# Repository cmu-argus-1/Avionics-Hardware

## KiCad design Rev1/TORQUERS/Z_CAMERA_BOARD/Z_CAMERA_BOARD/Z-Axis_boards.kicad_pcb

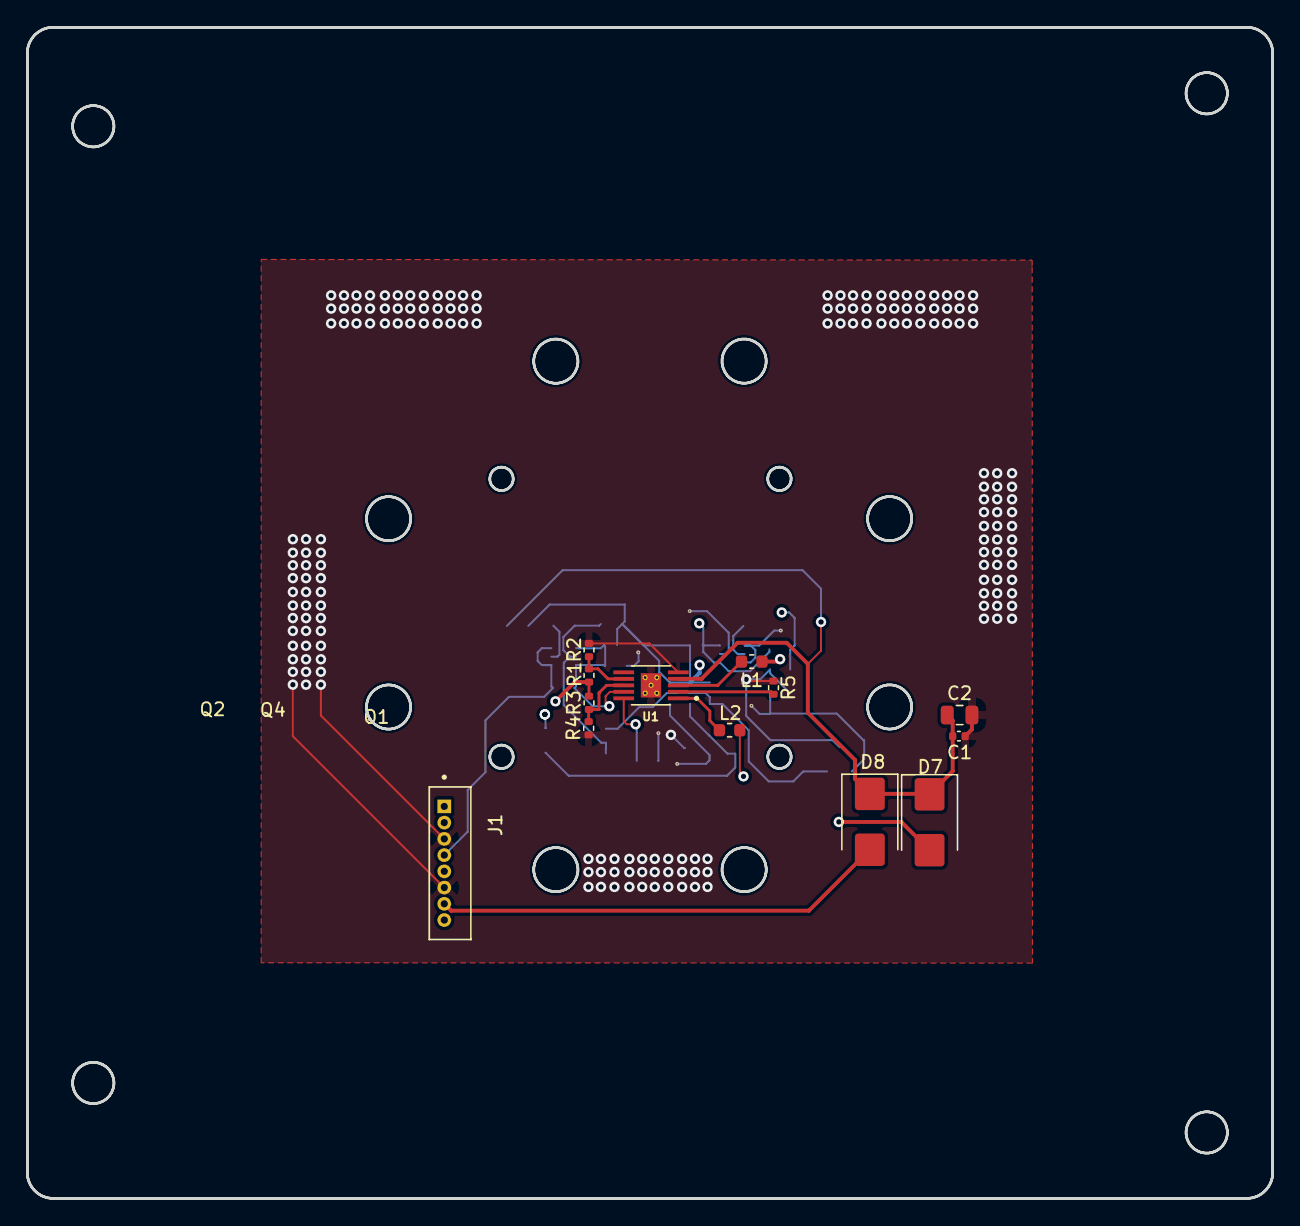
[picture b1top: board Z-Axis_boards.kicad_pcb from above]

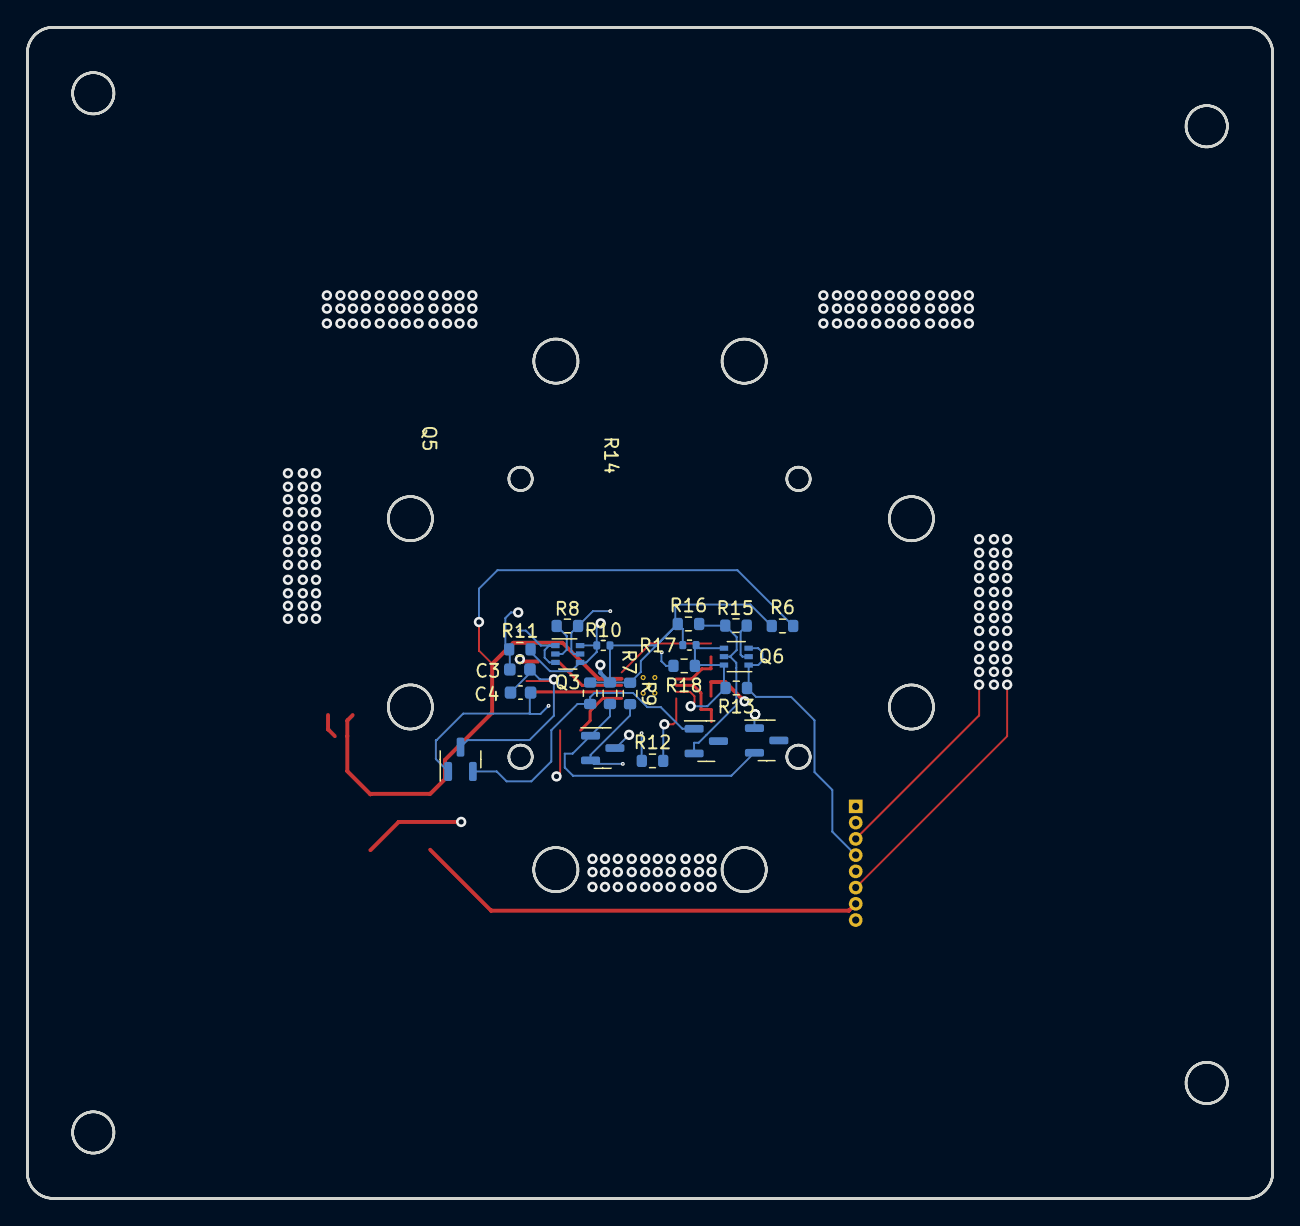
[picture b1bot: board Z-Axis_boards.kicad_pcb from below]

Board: 8 copper layers, 95.9 x 90.2 mm, 34 parts (21 on the bottom side), 22 nets.

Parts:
C1: 0.1uF; C_0402_1005Metric
C2: 10uF; C_0805_2012Metric
C3, C4: 10nF; C_0603_1608Metric
D7, D8: B220; D_SMB
J1: 0530470810; MOLEX_0530470810
L1, L2: TBD; L_0603_1608Metric
Q1, Q2, Q4, Q5: BSS138; SOT-23
Q3, Q6: MBT2222ADW1T1; SOT-363_SC-70-6
R1, R2, R3, R4, R5: 0; R_0402_1005Metric
R6, R12, R13: 0; R_0603_1608Metric
R7, R9, R14, R16: 10K; R_0603_1608Metric
R8, R15: 600; R_0603_1608Metric
R10, R17: 10K; R_0402_1005Metric
R11, R18: 100K; R_0603_1608Metric
U1: DRV8830DGQ; IC_XTR111AIDGQR

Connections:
+3.3V: D7.2 (A), J1.8, R1.2, R3.2, R6.1, R7.2, R9.1, R10.2, R14.2, R16.1, R17.2
/coils: L1.1, L2.1
GND: C1.2, C2.2, C3.2, C4.2, J1.3, J1.6, Q1.3 (D), Q2.3 (D), Q4.3 (D), Q5.3 (D), R2.1, R4.1, R5.2, U1.5 (GND), U1.11 (EP)
unnamed: C1.1, C2.1, D7.1 (K), D8.1 (K), R6.2, U1.4 (VCC)
unnamed: Q1.1 (G), Q2.2 (S), R7.1
unnamed: Q1.2 (S), Q3.5 (B2), R8.1, R9.2
unnamed: C3.1, Q2.1 (G), R11.1
unnamed: Q3.2 (B1), R8.2
unnamed: Q4.1 (G), Q5.2 (S), R14.1
unnamed: Q4.2 (S), Q6.5 (B2), R15.2, R16.2
unnamed: C4.1, Q5.1 (G), R18.1
unnamed: Q6.2 (B1), R15.1
unnamed: R1.1, R2.2, U1.7 (A0)
unnamed: R3.1, R4.2, U1.8 (A1)
unnamed: R5.1, U1.2 (ISENSE)
unnamed: L1.2, U1.3 (OUT1)
unnamed: L2.2, U1.1 (OUT2)
SCL: Q3.4 (E2), Q3.6 (C1), R10.1, R11.2, R12.2, U1.10 (SCL)
SCL1_b4iso: J1.5, Q3.1 (E1), Q3.3 (C2), R12.1
SDA: Q6.4 (E2), Q6.6 (C1), R13.2, R17.1, R18.2, U1.9 (SDA)
SDA1_b4iso: J1.4, Q6.1 (E1), Q6.3 (C2), R13.1
VBATT: D8.2 (A), J1.7

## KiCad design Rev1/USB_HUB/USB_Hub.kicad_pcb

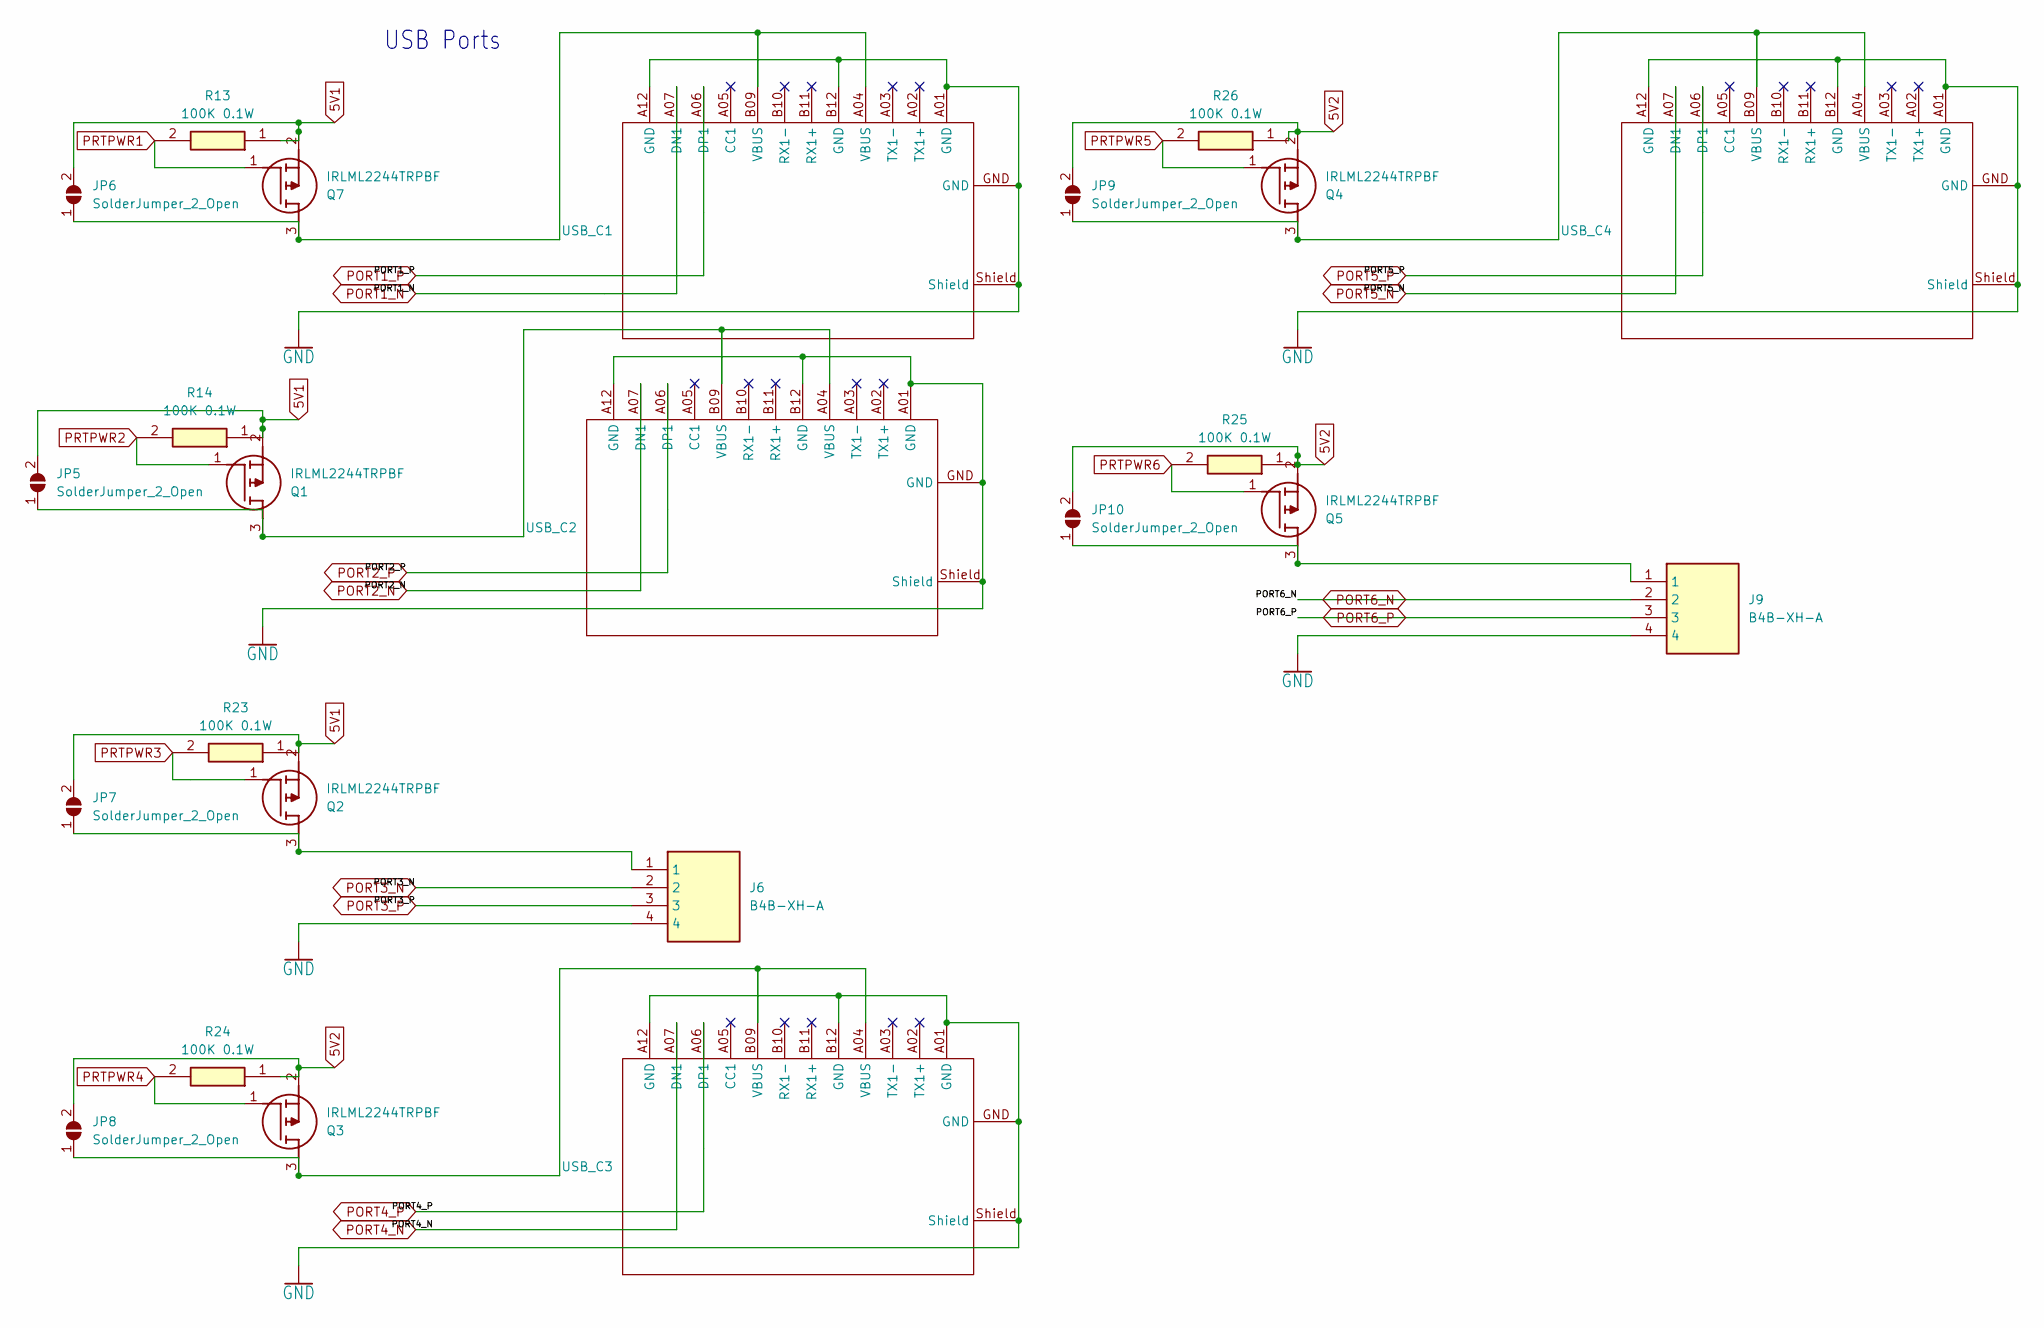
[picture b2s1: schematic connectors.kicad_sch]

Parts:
J6, J9: B4B-XH-A; B4BXHA; Manufacturer_Part_Number B4B-XH-A
JP5, JP6, JP7, JP8, JP9, JP10: SolderJumper_2_Open; SolderJumper-2_P1.3mm_Open_Pad1.0x1.5mm
Q1, Q2, Q3, Q4, Q5, Q7: IRLML2244TRPBF; SOT95P237X112-3N; Manufacturer_Part_Number IRLML2244TRPBF; Mouser Part Number 942-IRLML2244TRPBF
R13, R14, R23, R24, R25, R26: 100K 0.1W; RESC1608X55N; Manufacturer_Part_Number RMCF0603FT100K; Mouser Part Number 708-RMCF0603FT100K
USB_C1, USB_C2, USB_C3, USB_C4: PLUG-USBC-121SMT-4BS2S

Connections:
5V1: JP5.2 (B), JP6.2 (B), JP7.2 (B), Q1.2 (S), Q2.2 (S), Q7.2 (S), R13.1, R14.1, R23.1; also elsewhere on the board
5V2: JP8.2 (B), JP9.2 (B), JP10.2 (B), Q3.2 (S), Q4.2 (S), Q5.2 (S), R24.1, R25.1, R26.1; also elsewhere on the board
GND: J6.4, J9.4, USB_C1.A01 (GND), USB_C1.A12 (GND), USB_C1.B12 (GND), USB_C1.GND, USB_C1.Shield, USB_C2.A01 (GND), USB_C2.A12 (GND), USB_C2.B12 (GND), USB_C2.GND, USB_C2.Shield, USB_C3.A01 (GND), USB_C3.A12 (GND), USB_C3.B12 (GND), USB_C3.GND, USB_C3.Shield, USB_C4.A01 (GND), USB_C4.A12 (GND), USB_C4.B12 (GND), USB_C4.GND, USB_C4.Shield; also elsewhere on the board
unnamed: JP5.1 (A), Q1.3 (D), USB_C2.A04 (VBUS), USB_C2.B09 (VBUS)
unnamed: JP6.1 (A), Q7.3 (D), USB_C1.A04 (VBUS), USB_C1.B09 (VBUS)
unnamed: J6.1, JP7.1 (A), Q2.3 (D)
unnamed: JP8.1 (A), Q3.3 (D), USB_C3.A04 (VBUS), USB_C3.B09 (VBUS)
unnamed: JP9.1 (A), Q4.3 (D), USB_C4.A04 (VBUS), USB_C4.B09 (VBUS)
unnamed: J9.1, JP10.1 (A), Q5.3 (D)
PORT1_N: USB_C1.A07 (DN1); also elsewhere on the board
PORT1_P: USB_C1.A06 (DP1); also elsewhere on the board
PORT2_N: USB_C2.A07 (DN1); also elsewhere on the board
PORT2_P: USB_C2.A06 (DP1); also elsewhere on the board
PORT3_N: J6.2; also elsewhere on the board
PORT3_P: J6.3; also elsewhere on the board
PORT4_N: USB_C3.A07 (DN1); also elsewhere on the board
PORT4_P: USB_C3.A06 (DP1); also elsewhere on the board
PORT5_N: USB_C4.A07 (DN1); also elsewhere on the board
PORT5_P: USB_C4.A06 (DP1); also elsewhere on the board
PORT6_N: J9.2; also elsewhere on the board
PORT6_P: J9.3; also elsewhere on the board
PRTPWR1: Q7.1 (G), R13.2; also elsewhere on the board
PRTPWR2: Q1.1 (G), R14.2; also elsewhere on the board
PRTPWR3: Q2.1 (G), R23.2; also elsewhere on the board
PRTPWR4: Q3.1 (G), R24.2; also elsewhere on the board
PRTPWR5: Q4.1 (G), R26.2; also elsewhere on the board
PRTPWR6: Q5.1 (G), R25.2; also elsewhere on the board

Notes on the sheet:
USB Ports

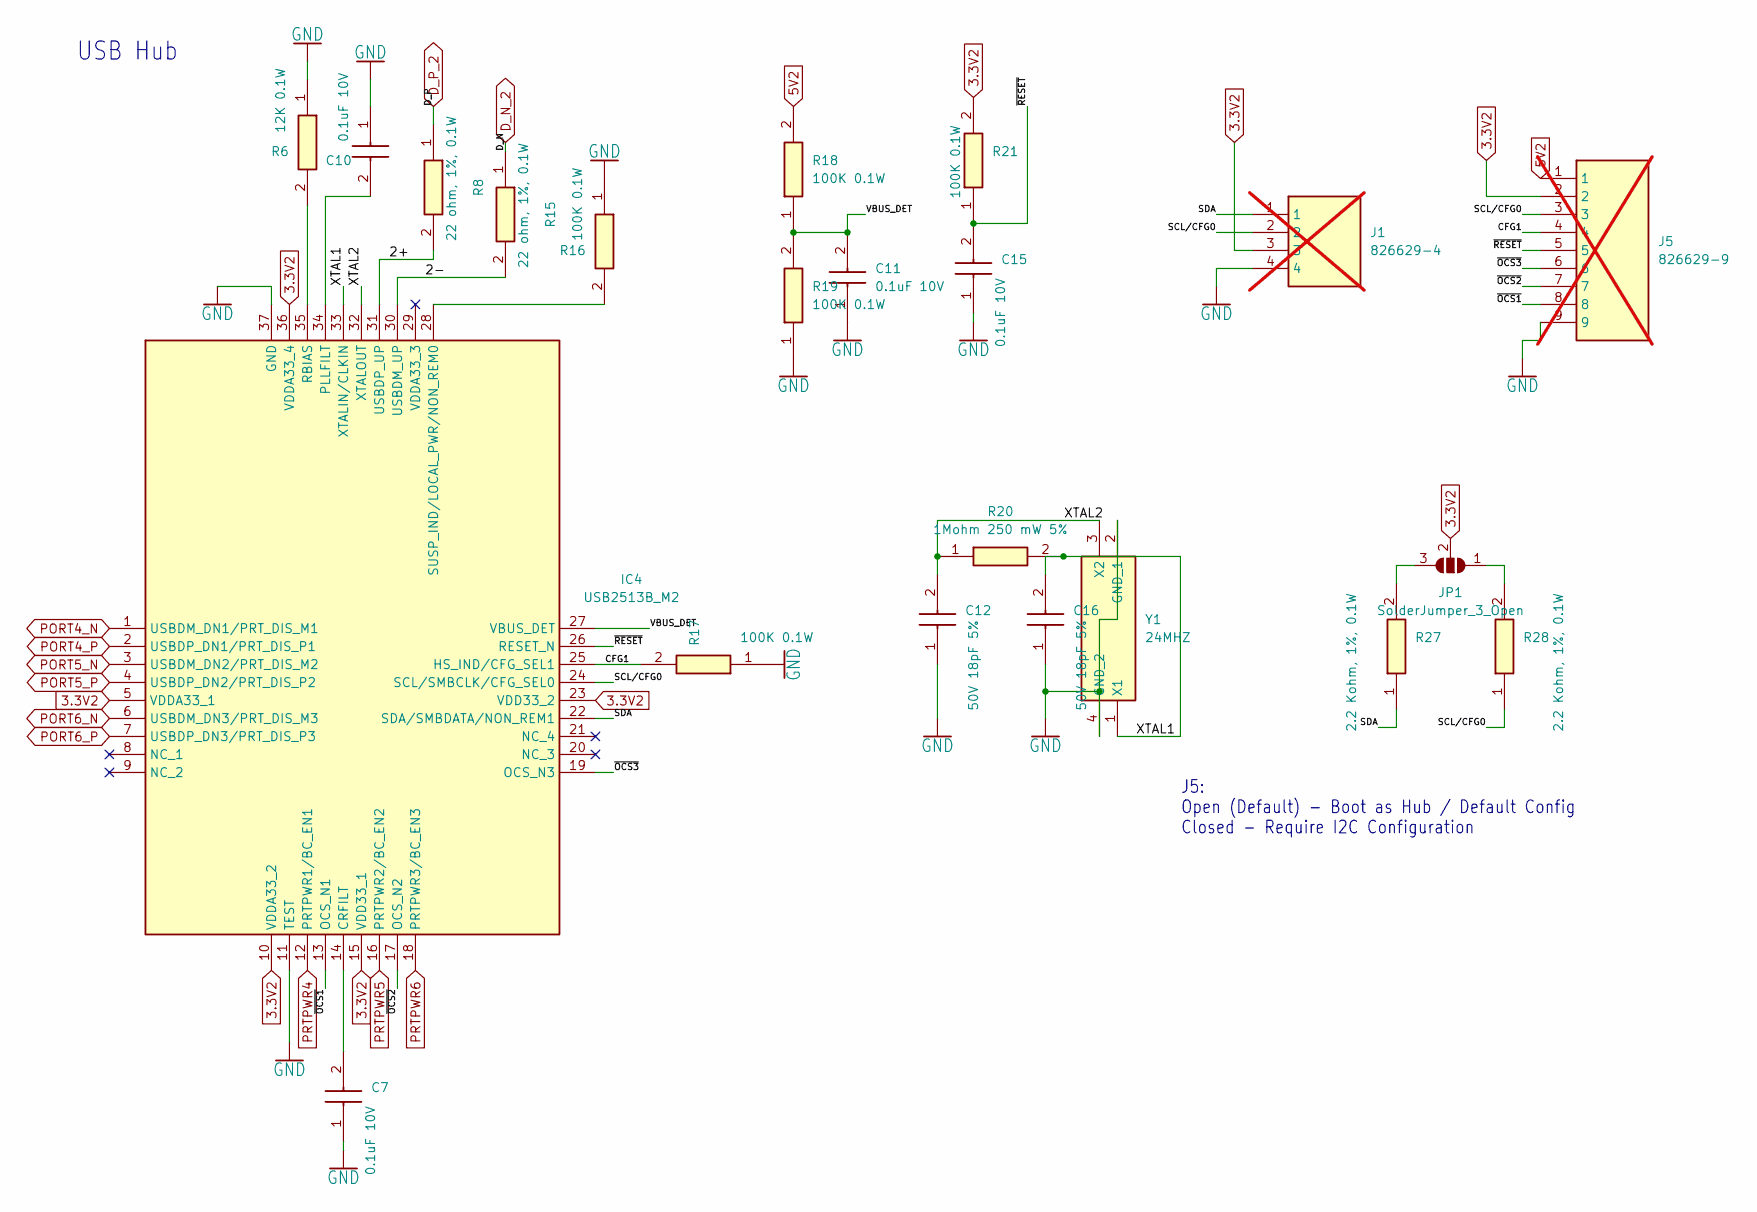
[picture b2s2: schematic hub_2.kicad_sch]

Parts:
C7, C10, C11, C15: 0.1uF 10V; CAPC1608X87N; Manufacturer_Part_Number C0603T104K8RAC7867; Mouser Part Number 80-C0603T104K8RACTU
C12, C16: 50V 18pF 5%; CAPC1608X90N; Manufacturer_Part_Number 06035A180J4T2A; Mouser Part Number 581-06035A180J4T2A
IC4: USB2513B_M2; QFN50P600X600X100-37N-D; Manufacturer_Part_Number USB2513B/M2; Mouser Part Number 579-USB2513B/M2
J1: 826629-4; HDRV4W63P0X254_1X4_1016X250X950P; Manufacturer_Part_Number 826629-4; Mouser Part Number 571-826629-4; not fitted
J5: 826629-9; HDRV9W63P0X254_1X9_2286X250X950P; Manufacturer_Part_Number 826629-9; Mouser Part Number 571-826629-9; not fitted
JP1: SolderJumper_3_Open; SolderJumper-3_P1.3mm_Open_Pad1.0x1.5mm_NumberLabels
R6: 12K 0.1W; RESC1608X55N; Manufacturer_Part_Number RMCF0603FT12K0
R8, R15: 22 ohm, 1%, 0.1W; RESC1608X55N; Manufacturer_Part_Number RMCF0603FT22R0
R16, R17, R18, R19, R21: 100K 0.1W; RESC1608X55N; Manufacturer_Part_Number RMCF0603FT100K; Mouser Part Number 708-RMCF0603FT100K
R20: 1Mohm 250 mW 5%; ERJP03_PA3__0603_; Manufacturer_Part_Number ERJ-PA3J105V; Mouser Part Number 667-ERJ-PA3J105V
R27, R28: 2.2 Kohm, 1%, 0.1W; RESC1608X55N; Manufacturer_Part_Number RMCF0603FT2K20
Y1: 24MHZ; ABM10W240000MHZ8K1ZT3; Manufacturer_Part_Number ABM10W-24.0000MHZ-7-B1U-T3

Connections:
3.3V2: IC4.5 (VDDA33_1), IC4.10 (VDDA33_2), IC4.15 (VDD33_1), IC4.23 (VDD33_2), IC4.36 (VDDA33_4), J1.3, J5.2, JP1.2 (C), R21.2; also elsewhere on the board
5V2: J5.1, R18.2; also elsewhere on the board
/hub_2/2+: IC4.31 (USBDP_UP), R8.2
/hub_2/2-: IC4.30 (USBDM_UP), R15.2
/hub_2/CFG1: IC4.25 (HS_IND/CFG_SEL1), J5.4, R17.2
/hub_2/SCL/CFG0: IC4.24 (SCL/SMBCLK/CFG_SEL0), J1.2, J5.3, R28.1
/hub_2/SDA: IC4.22 (SDA/SMBDATA/NON_REM1), J1.1, R27.1
/hub_2/VBUS_DET: C11.2, IC4.27 (VBUS_DET), R18.1, R19.2
/hub_2/XTAL1: C16.2, IC4.33 (XTALIN/CLKIN), R20.2, Y1.1 (X1)
/hub_2/XTAL2: C12.2, IC4.32 (XTALOUT), R20.1, Y1.3 (X2)
/hub_2/~OCS1: IC4.13 (OCS_N1), J5.8
/hub_2/~OCS2: IC4.17 (OCS_N2), J5.7
/hub_2/~OCS3: IC4.19 (OCS_N3), J5.6
/hub_2/~RESET: C15.2, IC4.26 (RESET_N), J5.5, R21.1
D_N_2: R15.1; also elsewhere on the board
D_P_2: R8.1; also elsewhere on the board
GND: C7.1, C10.1, C11.1, C12.1, C15.1, C16.1, IC4.11 (TEST), IC4.37 (GND), J1.4, J5.9, R6.1, R16.1, R17.1, R19.1, Y1.2 (GND_1), Y1.4 (GND_2); also elsewhere on the board
unnamed: C7.2, IC4.14 (CRFILT)
unnamed: C10.2, IC4.34 (PLLFILT)
unnamed: IC4.35 (RBIAS), R6.2
unnamed: IC4.28 (SUSP_IND/LOCAL_PWR/NON_REM0), R16.2
unnamed: JP1.1 (A), R28.2
unnamed: JP1.3 (B), R27.2
PORT4_N: IC4.1 (USBDM_DN1/PRT_DIS_M1); also elsewhere on the board
PORT4_P: IC4.2 (USBDP_DN1/PRT_DIS_P1); also elsewhere on the board
PORT5_N: IC4.3 (USBDM_DN2/PRT_DIS_M2); also elsewhere on the board
PORT5_P: IC4.4 (USBDP_DN2/PRT_DIS_P2); also elsewhere on the board
PORT6_N: IC4.6 (USBDM_DN3/PRT_DIS_M3); also elsewhere on the board
PORT6_P: IC4.7 (USBDP_DN3/PRT_DIS_P3); also elsewhere on the board
PRTPWR4: IC4.12 (PRTPWR1/BC_EN1); also elsewhere on the board
PRTPWR5: IC4.16 (PRTPWR2/BC_EN2); also elsewhere on the board
PRTPWR6: IC4.18 (PRTPWR3/BC_EN3); also elsewhere on the board

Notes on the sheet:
J5: Open (Default) - Boot as Hub / Default Config Closed - Require I2C Configuration
USB Hub

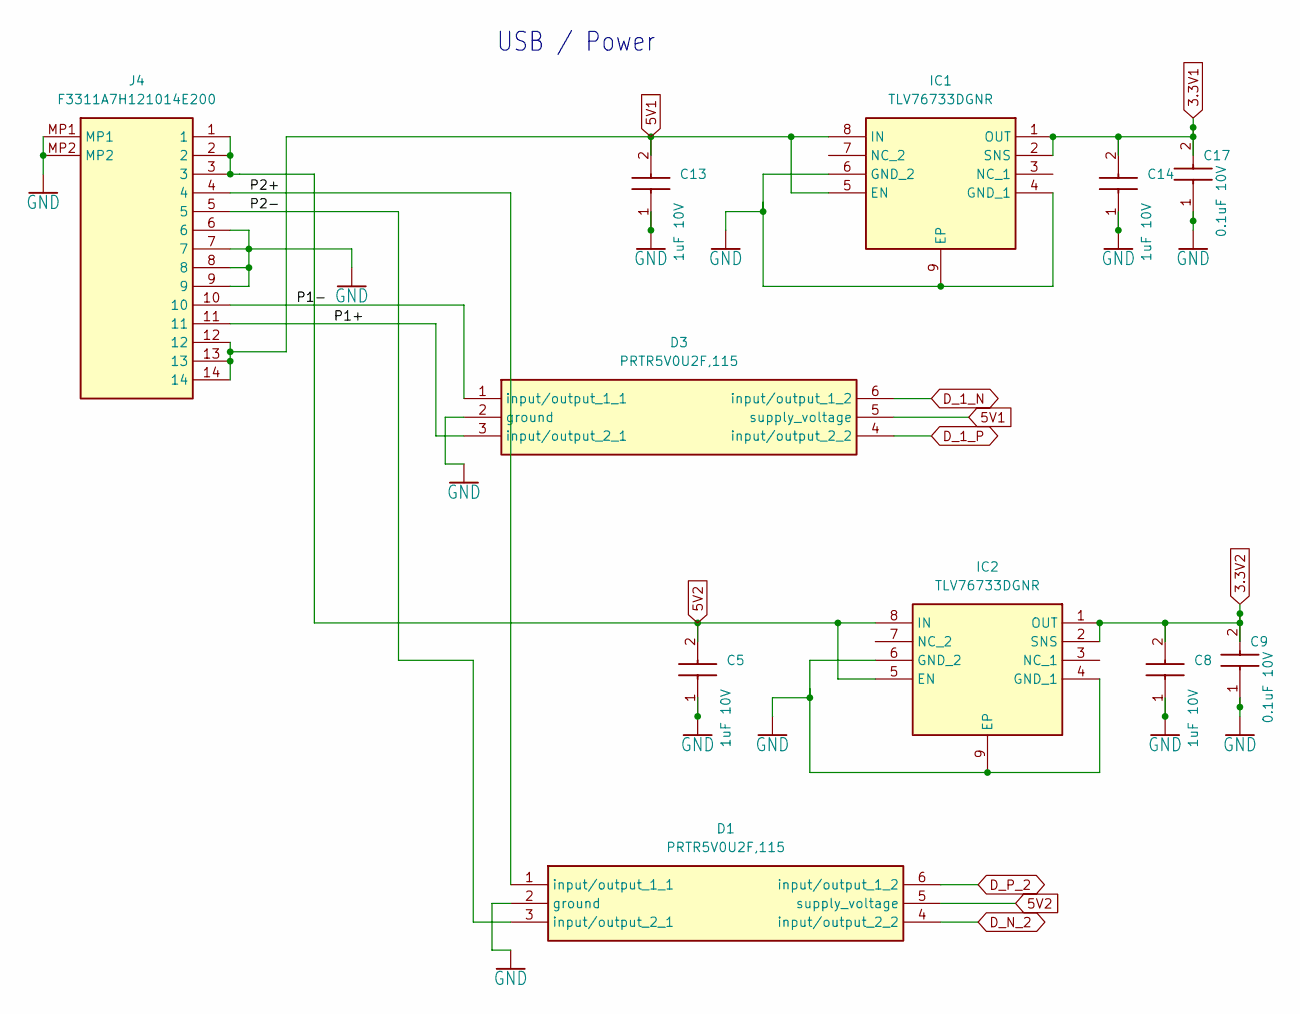
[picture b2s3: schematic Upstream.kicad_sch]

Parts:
C5, C8, C13, C14: 1uF 10V; CAPC1608X95N; Manufacturer_Part_Number CL10B105KB8NQNC; Mouser Part Number 187-CL10B105KB8NQNC
C9, C17: 0.1uF 10V; CAPC1608X87N; Manufacturer_Part_Number C0603T104K8RAC7867; Mouser Part Number 80-C0603T104K8RACTU
D1, D3: PRTR5V0U2F,115; PESD3V3L5UF115; Manufacturer_Part_Number PRTR5V0U2F,115; Mouser Part Number 771-PRTR5V0U2F-T/R
IC1, IC2: TLV76733DGNR; SOP65P490X110-9N; Manufacturer_Part_Number TLV76733DGNR; Mouser Part Number 595-TLV76733DGNR
J4: F3311A7H121014E200; Manufacturer_Part_Number F3311A7H121014E200

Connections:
3.3V1: C14.2, C17.2, IC1.1 (OUT), IC1.2 (SNS); also elsewhere on the board
3.3V2: C8.2, C9.2, IC2.1 (OUT), IC2.2 (SNS); also elsewhere on the board
5V1: C13.2, D3.5 (supply_voltage), IC1.5 (EN), IC1.8 (IN), J4.12, J4.13, J4.14; also elsewhere on the board
5V2: C5.2, D1.5 (supply_voltage), IC2.5 (EN), IC2.8 (IN), J4.1, J4.2, J4.3; also elsewhere on the board
/Upstream/P1+: D3.3 (input/output_2_1), J4.11
/Upstream/P1-: D3.1 (input/output_1_1), J4.10
/Upstream/P2+: D1.1 (input/output_1_1), J4.4
/Upstream/P2-: D1.3 (input/output_2_1), J4.5
D_1_N: D3.6 (input/output_1_2); also elsewhere on the board
D_1_P: D3.4 (input/output_2_2); also elsewhere on the board
D_N_2: D1.4 (input/output_2_2); also elsewhere on the board
D_P_2: D1.6 (input/output_1_2); also elsewhere on the board
GND: C5.1, C8.1, C9.1, C13.1, C14.1, C17.1, D1.2 (ground), D3.2 (ground), IC1.4 (GND_1), IC1.6 (GND_2), IC1.9 (EP), IC2.4 (GND_1), IC2.6 (GND_2), IC2.9 (EP), J4.6, J4.7, J4.8, J4.9, J4.MP1, J4.MP2; also elsewhere on the board

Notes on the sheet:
USB / Power

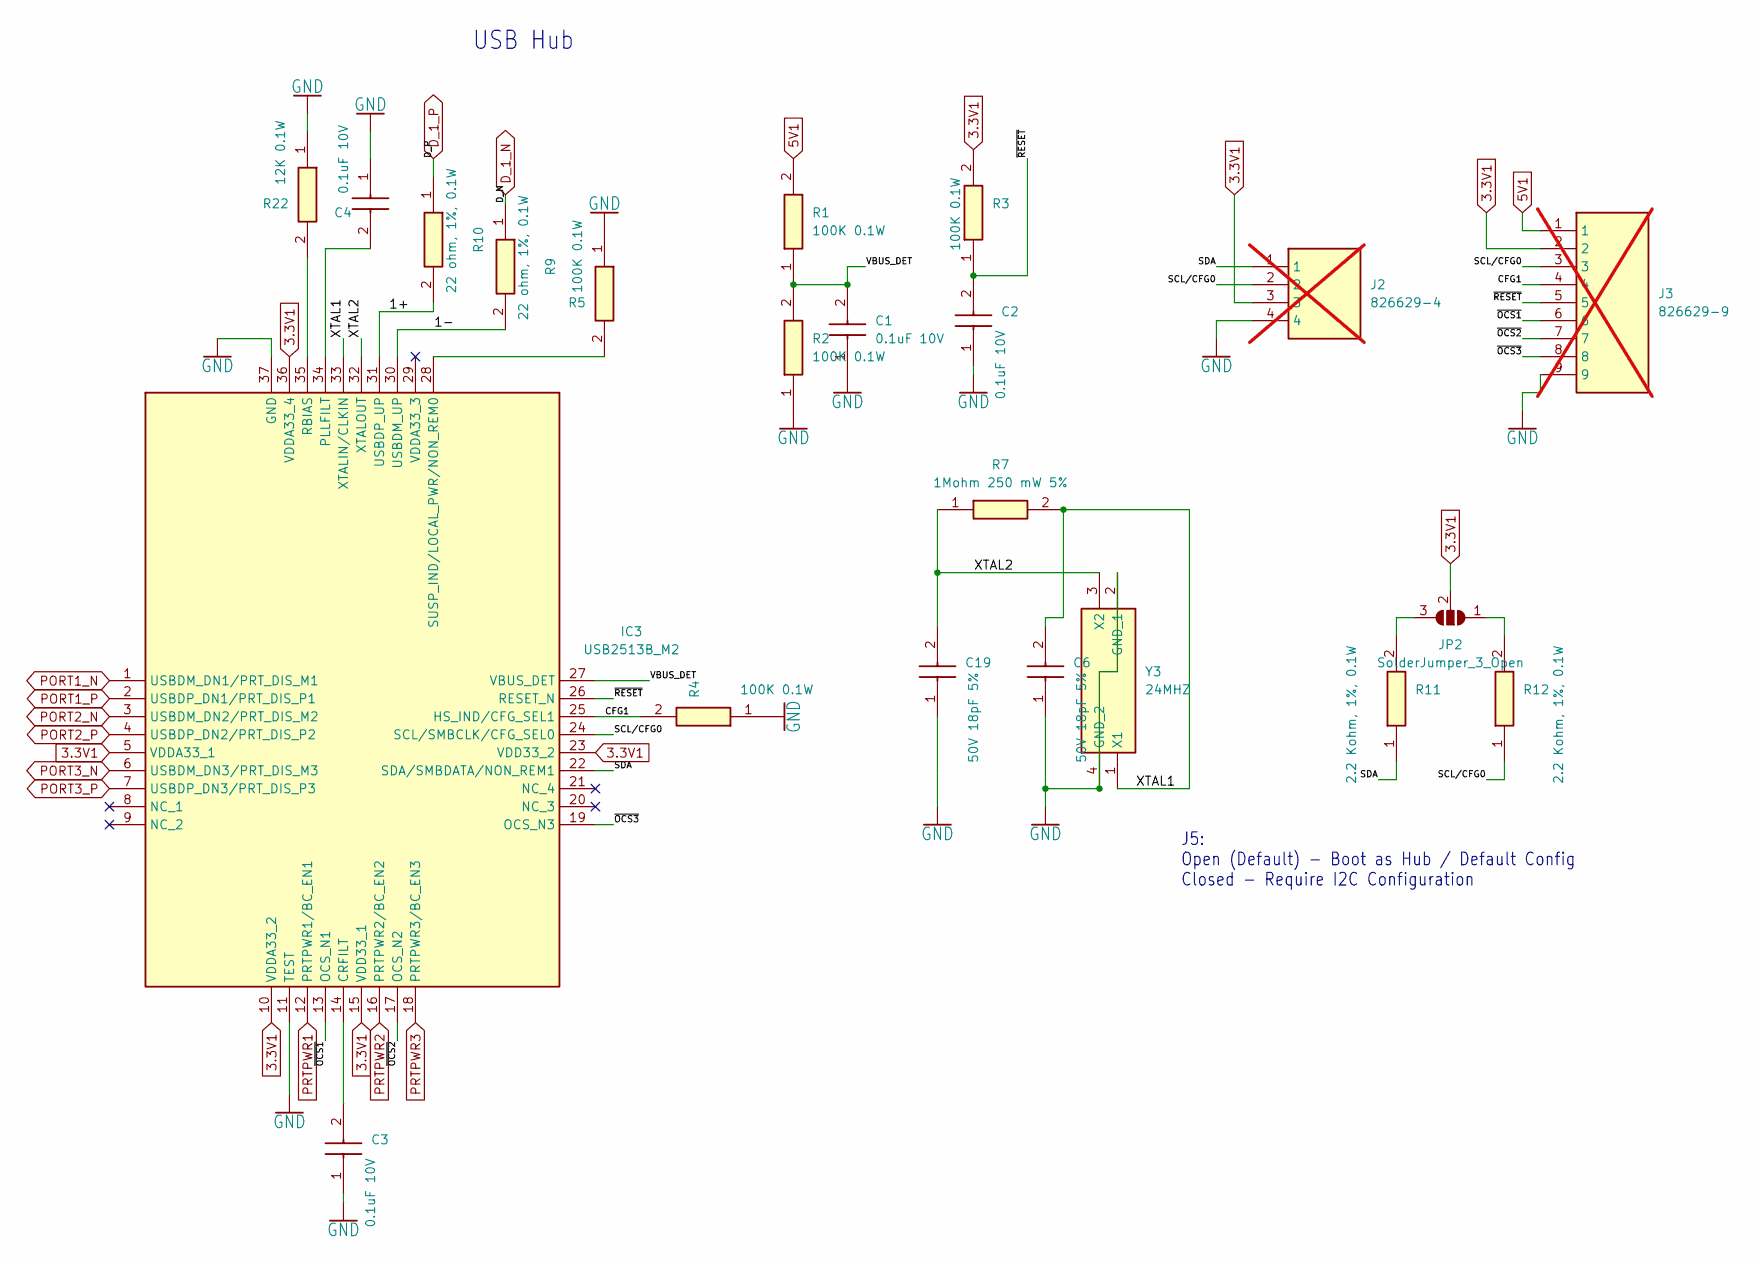
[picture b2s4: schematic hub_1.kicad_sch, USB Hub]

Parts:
C1, C2, C3, C4: 0.1uF 10V; CAPC1608X87N; Manufacturer_Part_Number C0603T104K8RAC7867; Mouser Part Number 80-C0603T104K8RACTU
C6, C19: 50V 18pF 5%; CAPC1608X90N; Manufacturer_Part_Number 06035A180J4T2A; Mouser Part Number 581-06035A180J4T2A
IC3: USB2513B_M2; QFN50P600X600X100-37N-D; Manufacturer_Part_Number USB2513B/M2; Mouser Part Number 579-USB2513B/M2
J2: 826629-4; HDRV4W63P0X254_1X4_1016X250X950P; Manufacturer_Part_Number 826629-4; Mouser Part Number 571-826629-4; not fitted
J3: 826629-9; HDRV9W63P0X254_1X9_2286X250X950P; Manufacturer_Part_Number 826629-9; Mouser Part Number 571-826629-9; not fitted
JP2: SolderJumper_3_Open; SolderJumper-3_P1.3mm_Open_Pad1.0x1.5mm_NumberLabels
R1, R2, R3, R4, R5: 100K 0.1W; RESC1608X55N; Manufacturer_Part_Number RMCF0603FT100K; Mouser Part Number 708-RMCF0603FT100K
R7: 1Mohm 250 mW 5%; ERJP03_PA3__0603_; Manufacturer_Part_Number ERJ-PA3J105V; Mouser Part Number 667-ERJ-PA3J105V
R9, R10: 22 ohm, 1%, 0.1W; RESC1608X55N; Manufacturer_Part_Number RMCF0603FT22R0
R11, R12: 2.2 Kohm, 1%, 0.1W; RESC1608X55N; Manufacturer_Part_Number RMCF0603FT2K20
R22: 12K 0.1W; RESC1608X55N; Manufacturer_Part_Number RMCF0603FT12K0
Y3: 24MHZ; ABM10W240000MHZ8K1ZT3; Manufacturer_Part_Number ABM10W-24.0000MHZ-7-B1U-T3

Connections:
3.3V1: IC3.5 (VDDA33_1), IC3.10 (VDDA33_2), IC3.15 (VDD33_1), IC3.23 (VDD33_2), IC3.36 (VDDA33_4), J2.3, J3.2, JP2.2 (C), R3.2; also elsewhere on the board
5V1: J3.1, R1.2; also elsewhere on the board
/hub_1/1+: IC3.31 (USBDP_UP), R10.2
/hub_1/1-: IC3.30 (USBDM_UP), R9.2
/hub_1/CFG1: IC3.25 (HS_IND/CFG_SEL1), J3.4, R4.2
/hub_1/SCL/CFG0: IC3.24 (SCL/SMBCLK/CFG_SEL0), J2.2, J3.3, R12.1
/hub_1/SDA: IC3.22 (SDA/SMBDATA/NON_REM1), J2.1, R11.1
/hub_1/VBUS_DET: C1.2, IC3.27 (VBUS_DET), R1.1, R2.2
/hub_1/XTAL1: C6.2, IC3.33 (XTALIN/CLKIN), R7.2, Y3.1 (X1)
/hub_1/XTAL2: C19.2, IC3.32 (XTALOUT), R7.1, Y3.3 (X2)
/hub_1/~OCS1: IC3.13 (OCS_N1), J3.6
/hub_1/~OCS2: IC3.17 (OCS_N2), J3.7
/hub_1/~OCS3: IC3.19 (OCS_N3), J3.8
/hub_1/~RESET: C2.2, IC3.26 (RESET_N), J3.5, R3.1
D_1_N: R9.1; also elsewhere on the board
D_1_P: R10.1; also elsewhere on the board
GND: C1.1, C2.1, C3.1, C4.1, C6.1, C19.1, IC3.11 (TEST), IC3.37 (GND), J2.4, J3.9, R2.1, R4.1, R5.1, R22.1, Y3.2 (GND_1), Y3.4 (GND_2); also elsewhere on the board
unnamed: C3.2, IC3.14 (CRFILT)
unnamed: C4.2, IC3.34 (PLLFILT)
unnamed: IC3.35 (RBIAS), R22.2
unnamed: IC3.28 (SUSP_IND/LOCAL_PWR/NON_REM0), R5.2
unnamed: JP2.1 (A), R12.2
unnamed: JP2.3 (B), R11.2
PORT1_N: IC3.1 (USBDM_DN1/PRT_DIS_M1); also elsewhere on the board
PORT1_P: IC3.2 (USBDP_DN1/PRT_DIS_P1); also elsewhere on the board
PORT2_N: IC3.3 (USBDM_DN2/PRT_DIS_M2); also elsewhere on the board
PORT2_P: IC3.4 (USBDP_DN2/PRT_DIS_P2); also elsewhere on the board
PORT3_N: IC3.6 (USBDM_DN3/PRT_DIS_M3); also elsewhere on the board
PORT3_P: IC3.7 (USBDP_DN3/PRT_DIS_P3); also elsewhere on the board
PRTPWR1: IC3.12 (PRTPWR1/BC_EN1); also elsewhere on the board
PRTPWR2: IC3.16 (PRTPWR2/BC_EN2); also elsewhere on the board
PRTPWR3: IC3.18 (PRTPWR3/BC_EN3); also elsewhere on the board

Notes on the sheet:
USB Hub
J5: Open (Default) - Boot as Hub / Default Config Closed - Require I2C Configuration

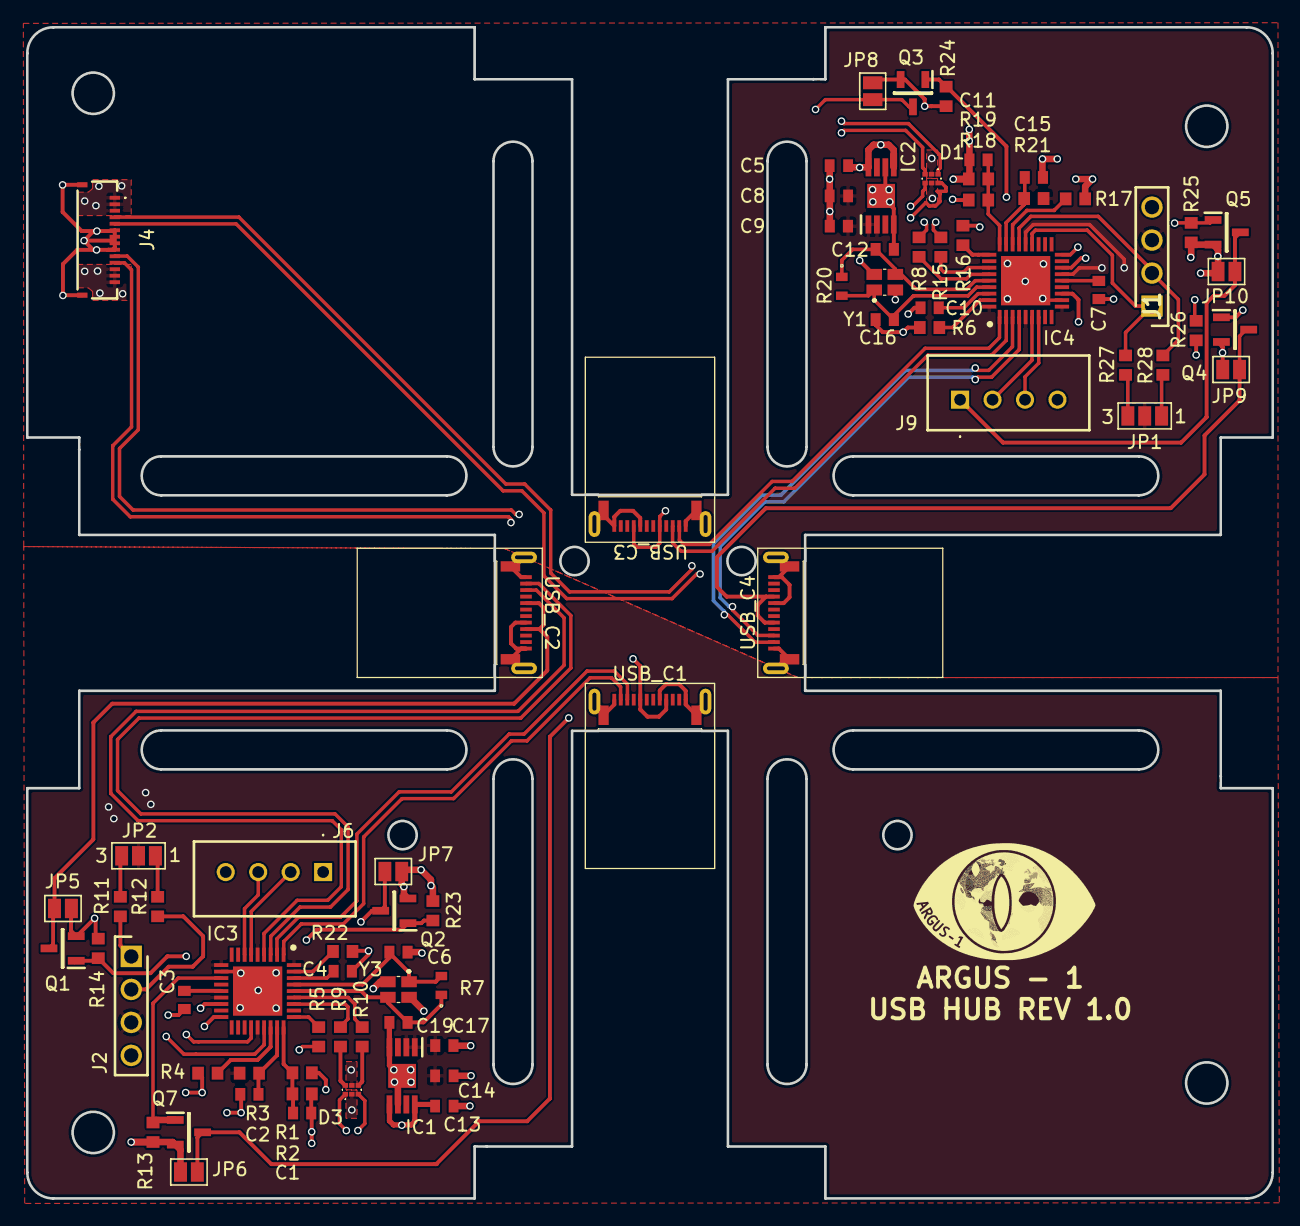
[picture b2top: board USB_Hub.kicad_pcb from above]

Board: 4 copper layers, 95.9 x 90.2 mm, 77 parts (0 on the bottom side), 67 nets.

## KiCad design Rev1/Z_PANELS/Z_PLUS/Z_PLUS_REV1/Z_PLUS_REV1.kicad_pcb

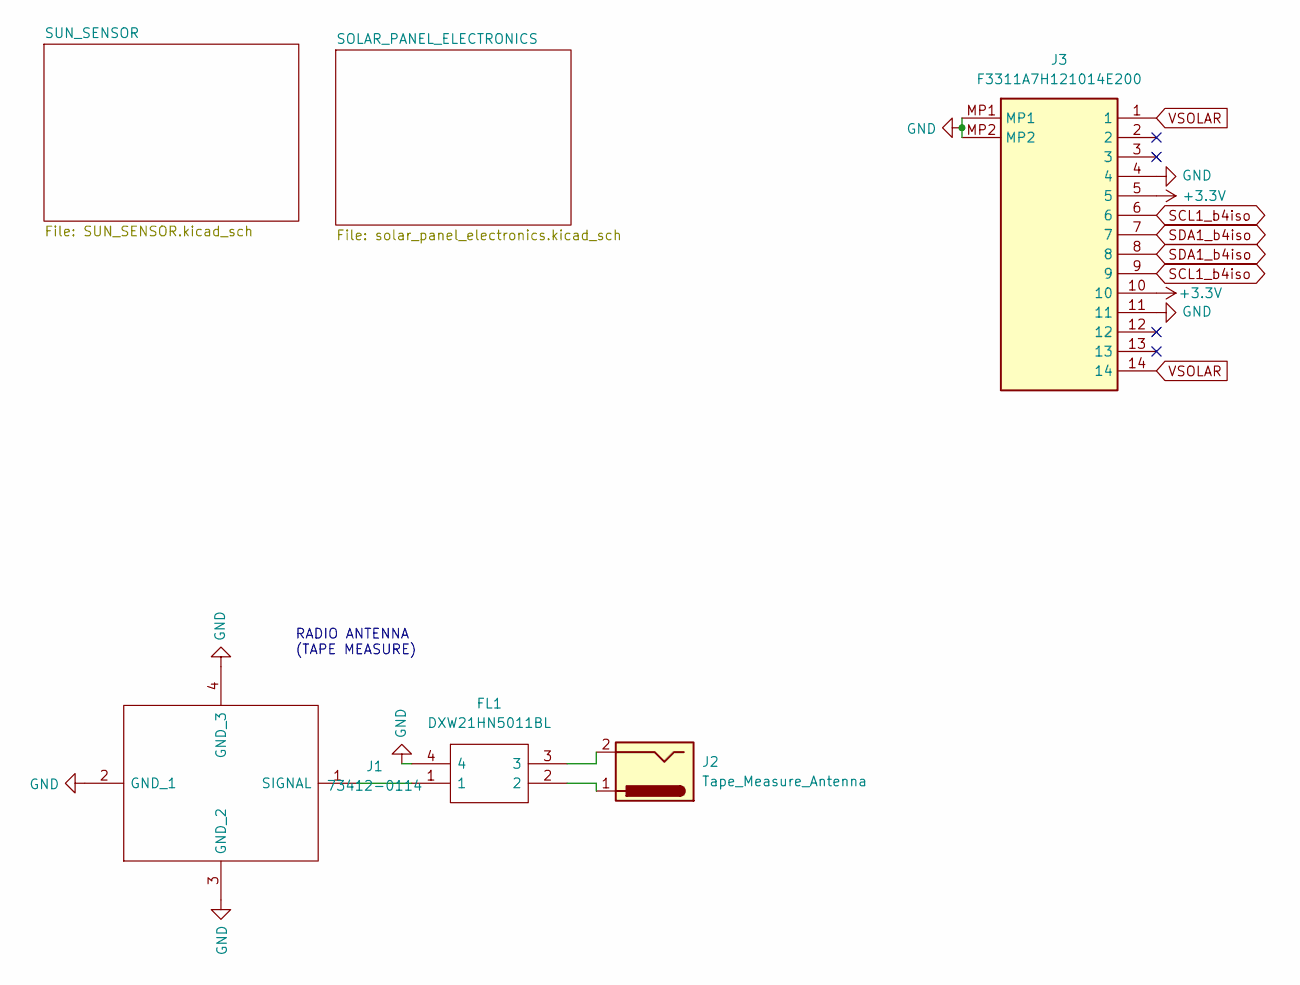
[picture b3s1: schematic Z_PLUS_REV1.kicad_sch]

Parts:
FL1: DXW21HN5011BL; Manufacturer_Part_Number DXW21HN5011BL; Mouser Part Number 81-DXW21HN5011BL
J1: 73412-0114; 73412-0110; Manufacturer_Part_Number 73412-0114; Mouser Part Number 538-73412-0114
J2: Tape_Measure_Antenna; Radio_antenna
J3: F3311A7H121014E200; Manufacturer_Part_Number F3311A7H121014E200

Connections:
/1+: FL1.3, J2.2
/1-: FL1.2, J2.1
GND: FL1.4, J1.2 (GND_1), J1.3 (GND_2), J1.4 (GND_3), J3.4, J3.11, J3.MP1, J3.MP2; also elsewhere on the board
unnamed: FL1.1, J1.1 (SIGNAL)
SCL1_b4iso: J3.6, J3.9; also elsewhere on the board
SDA1_b4iso: J3.7, J3.8; also elsewhere on the board
VSOLAR: J3.1, J3.14; also elsewhere on the board

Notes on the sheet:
RADIO ANTENNA (TAPE MEASURE)
